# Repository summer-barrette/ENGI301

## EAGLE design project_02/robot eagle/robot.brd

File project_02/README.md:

# MOOD-DRAWING ROBOT

Hackster Project can be found at 
https://www.hackster.io/summer-barrette/mood-drawing-robot-949c22.

# STORY

My project is a mood-drawing robot. The project was inspired by the idea of 
mood rings, which are fun accessories that change color based on the 
temperature around them. My robot contains a temperature sensor that is able to 
use body heat to distinguish between times when the user is not covering the 
sensor and times when the user is covering the sensor. The robot then decides 
either that it is that it is happy (the user was covering the sensor) or sad 
(the user was not covering the sensor). Finally, using wheels connected to the 
chassis and a pen connected to a servo, the robot moves around and draws the 
user a corresponding smiley or frowny face on a standard sheet of letter paper.

# PRINTED CIRCUIT BOARD DESIGN

This repository contains the files necessary for manufacturing a printed circuit 
board for the Mood-Drawing Robot. 
*   "robot docs" contains (1) the original proposal, (2) schematics as a PDF, 
    (3) top and bottom assembly views with associated dimensions, (4) a bill of
    materials, and (5) previews of the top and bottom layer Gerber files.
*   "robot eagle" contains all the Eagle files used to build the printed circuit
    board design including (1) library of components, (2) schematics, (3) design
    rules, and (4) layout of the board.
*   "robot mfg" contains all manufacturing files including Gerber files.

# PARTS LIST

*   1 Pocket Beagle
*   1 SG90 Micro-Servo Motor
*   1 L293x Quadruple Half-H Drivers
*   2 DC Gear Motors with Smart Car Robot Plastic Tire Wheel
*   2 Buttons (Yellow and Blue)
*   1 Pen Ink Cartridge
*   1 Wooden Dowel
*   1 Printed Ciruit Board with
    * 1 Adafruit Si7021 Temperature & Humidity Sensor
    * 2 LEDs (Yellow and Blue)
    * 2 1KΩ Resistors
    * 2 10KΩ Resistors
    * 1 0.1μF Capacitor

# BUILD INSTRUCTIONS

*   Solder Through-hole Components
    * Solder PocketBeagle to PocketBeagle Outline
    * Solder Adafruit Si7021 Temperature & Humidity Sensor to U3 Outline
    * Solder L293x Quadruple Half-H Drivers to U2 Outline
    * Solder SG90 Micro-Servo Motor wires to U4 power, signal, and ground pads
    * Solder DC Gear Motors to M1 and M2 power and ground pads
*   Construct Chassis
    * Laser cut chassis vector template out of foam core
    * Using hot glue, assemble foam chassis so that 
    * (first) the wheels and back wooden dowel are between levels 1 and 2.
    * (second) the PocketBeagle and servo are between levels 2 and 3.
    * (third) the solderless breadboard is above level 3.
    * (fourth) the front wooden dowel and pen go from the ground to above 
      level 2.
    * Tie the servo to the pen with a thin wire; ensure servo pushes pen down 
      into the ground when ‘on’ and pulls pen up off the ground when ‘off’.

# OPERATION INSTRUCTIONS

1.  Turn on PocketBeagle to run the run script
    * The pins should be configured.
    * The program should initialize.
2.	Press the yellow button while either covering or not covering the 
    temperature sensor
    * The yellow LED should turn on.
    * The temperature should be recorded and the mood (happy or sad) decided.
    * The yellow LED should turn off.
3.	Set the robot in the center of a standard sheet of letter paper
    * (first) the paper is in a vertical orientation.
    * (second) the wooden dowel is on the top left corner of the paper.
    * (third) the front of the robot is facing and parallel to the top edge 
      of the paper.
4.	Press the blue button
    * The blue light should come on.
    * The robot should drive around while picking up and putting down the pen.
    * The robot should draw a frowny or smiley face.
5.	The ‘temperature’ function and ‘drawing’ function do not have to be linear. 
    This means the temperature can be re-recorded by hitting the yellow button 
    directly after the previous temperature sequence. And the robot can re-draw 
    the same smiley or frowny face by hitting the blue button directly after 
    the previous drawing sequence.

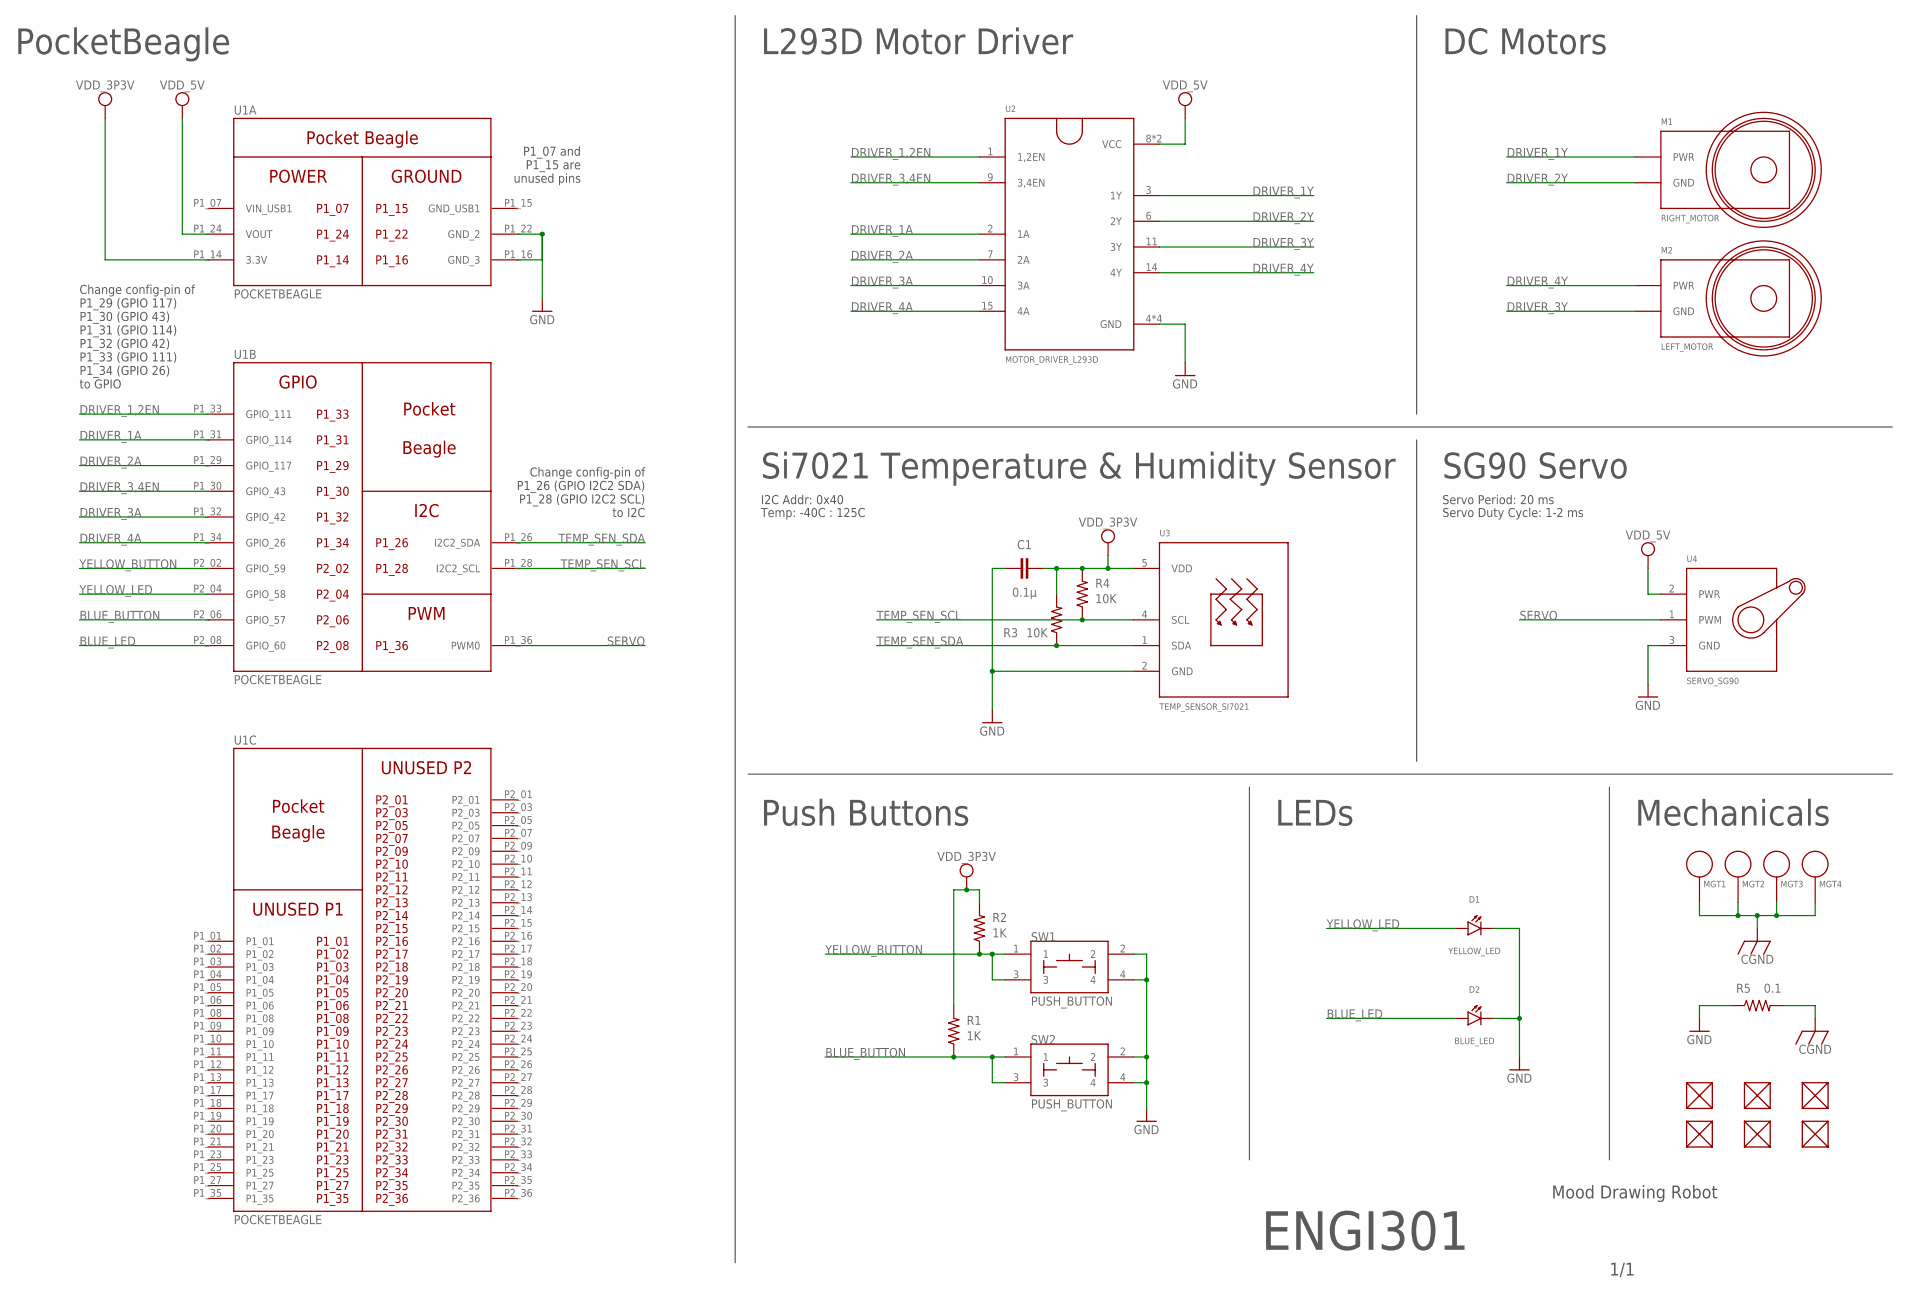
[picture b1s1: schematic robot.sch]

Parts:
C1: 0.1μ; C0603
D1: YELLOW_LED; LED_EIA_STD
D2: BLUE_LED; LED_EIA_STD
FUD1, FUD2, FUD3, FUD4, FUD5, FUD6: FIDUCIAL; FIDUCIAL_40MIL
M1: RIGHT_MOTOR; DC_MOTOR
M2: LEFT_MOTOR; DC_MOTOR
MGT1, MGT2, MGT3, MGT4: MOUNTING_HOLE
R1, R2: 1K; R0603
R3, R4: 10K; R0603
R5: 0.1; R0805
SW1, SW2: PUSH_BUTTON; PUSH_BUTTON_12.5MM
U1: POCKETBEAGLE
U2: MOTOR_DRIVER_L293D; MOTOR_DRIVER
U3: TEMP_SENSOR_SI7021; TEMP_SENSOR
U4: SERVO_SG90; SERVO

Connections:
BLUE_BUTTON: R1.1, SW2.1, SW2.3, U1.P2_06 (GPIO_57)
BLUE_LED: D2.ANODE, U1.P2_08 (GPIO_60)
CGND: MGT1.P$1, MGT2.P$1, MGT3.P$1, MGT4.P$1, R5.2
DRIVER_1,2EN: U1.P1_33 (GPIO_111), U2.1 (1,2EN)
DRIVER_1A: U1.P1_31 (GPIO_114), U2.2 (1A)
DRIVER_1Y: M1.1 (PWR), U2.3 (1Y)
DRIVER_2A: U1.P1_29 (GPIO_117), U2.7 (2A)
DRIVER_2Y: M1.2 (GND), U2.6 (2Y)
DRIVER_3,4EN: U1.P1_30 (GPIO_43), U2.9 (3,4EN)
DRIVER_3A: U1.P1_32 (GPIO_42), U2.10 (3A)
DRIVER_3Y: M2.2 (GND), U2.11 (3Y)
DRIVER_4A: U1.P1_34 (GPIO_26), U2.15 (4A)
DRIVER_4Y: M2.1 (PWR), U2.14 (4Y)
GND: C1.1, D1.CATHODE, D2.CATHODE, R5.1, SW1.2, SW1.4, SW2.2, SW2.4, U1.P1_16 (GND_3), U1.P1_22 (GND_2), U2.4 (GND), U2.5 (GND), U2.12 (GND), U2.13 (GND), U3.2 (GND), U4.3 (GND)
SERVO: U1.P1_36 (PWM0), U4.1 (PWM)
TEMP_SEN_SCL: R4.1, U1.P1_28 (I2C2_SCL), U3.4 (SCL)
TEMP_SEN_SDA: R3.1, U1.P1_26 (I2C2_SDA), U3.1 (SDA)
VDD_3P3V: C1.2, R1.2, R2.2, R3.2, R4.2, U1.P1_14 (3.3V), U3.5 (VDD)
VDD_5V: U1.P1_24 (VOUT), U2.8 (VCC), U2.16 (VCC), U4.2 (PWR)
VIN_USB1: U1.P1_07 (VIN_USB1)
YELLOW_BUTTON: R2.1, SW1.1, SW1.3, U1.P2_02 (GPIO_59)
YELLOW_LED: D1.ANODE, U1.P2_04 (GPIO_58)

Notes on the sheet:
PocketBeagle
L293D Motor Driver
DC Motors
Si7021 Temperature & Humidity Sensor
SG90 Servo
Push Buttons
LEDs
I2C Addr: 0x40
Servo Period: 20 ms
Servo Duty Cycle: 1-2 ms
1/1
Mood Drawing Robot
ENGI301
Mechanicals
Temp: -40C : 125C
Change config-pin of P1_29 (GPIO 117) P1_30 (GPIO 43) P1_31 (GPIO 114) P1_32 (GPIO 42) P1_33 (GPIO 111) P1_34 (GPIO 26) to GPIO
Change config-pin of P1_26 (GPIO I2C2 SDA) P1_28 (GPIO I2C2 SCL) to I2C
P1_07 and P1_15 are unused pins

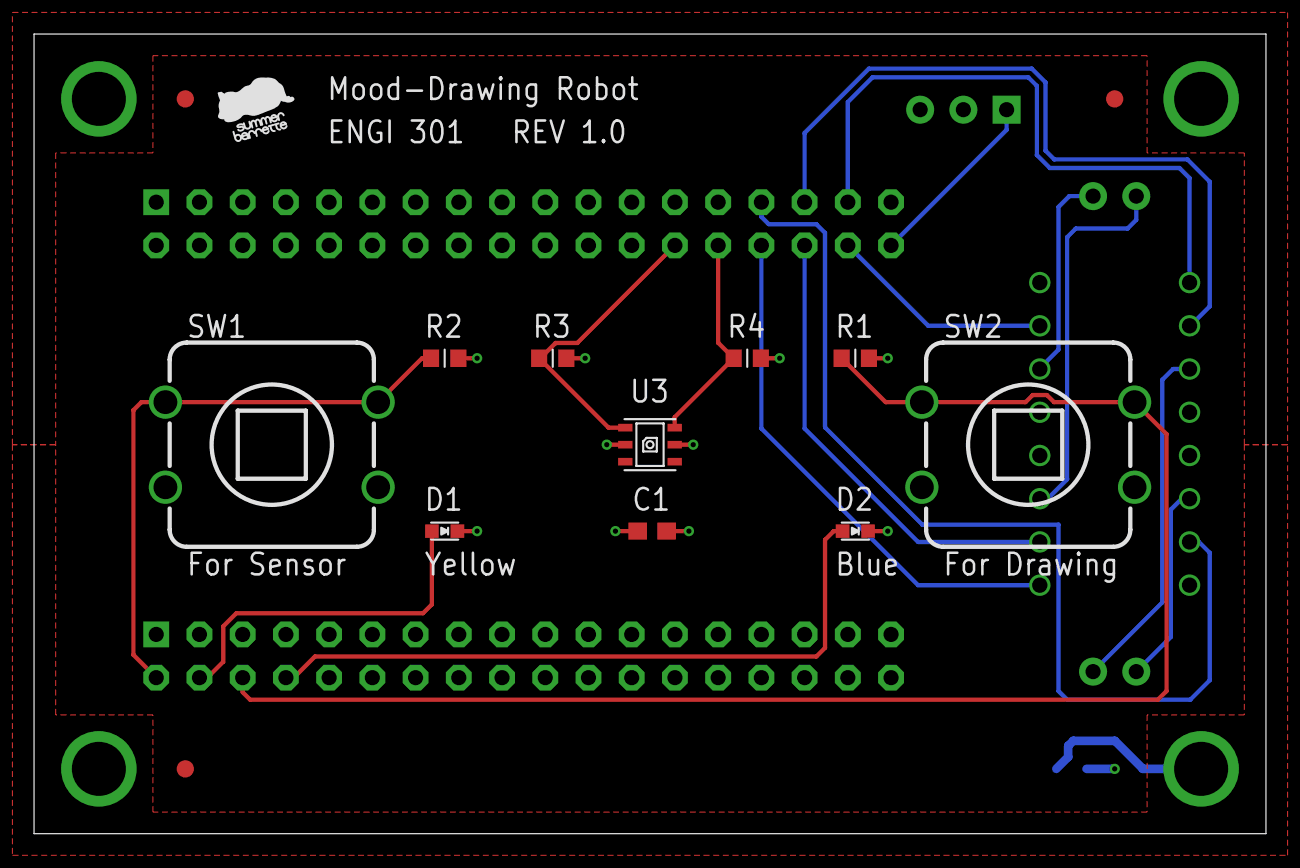
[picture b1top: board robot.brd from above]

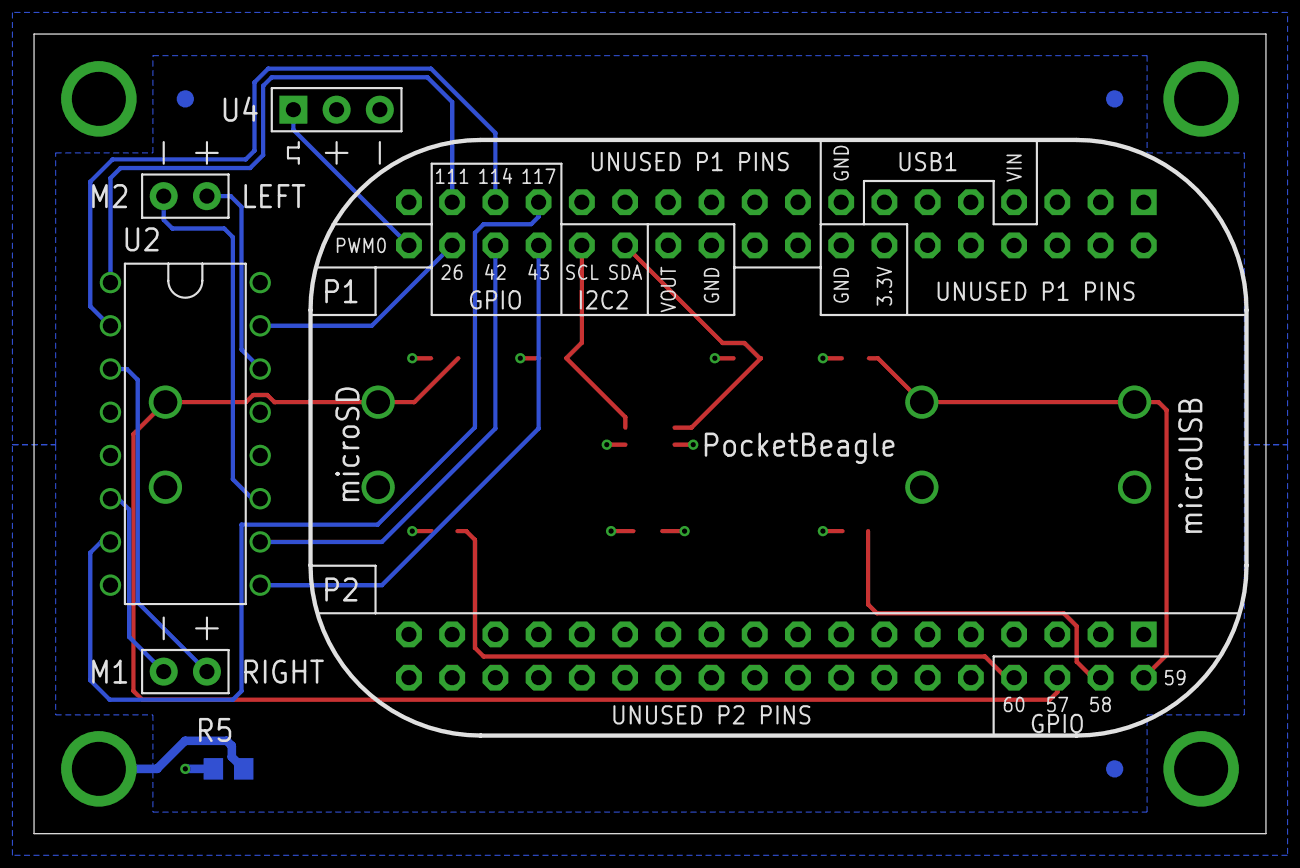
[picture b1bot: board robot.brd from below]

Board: 4 copper layers, 72.4 x 47.0 mm, 27 parts (9 on the bottom side), 21 nets.

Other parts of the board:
U$1: LOGO

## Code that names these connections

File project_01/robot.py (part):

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
SG90_FREQ   = 50                  # 20ms period (50Hz)
SG90_POL    = 0                   # Rising Edge polarity
SG90_OFF    = 5                   # 0ms pulse -- Servo is inactive
SG90_RIGHT  = 5                   # 1ms pulse (5% duty cycle)  -- All the way right
SG90_LEFT   = 10                  # 2ms pulse (10% duty cycle) -- All the way Left

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        """Setup the hardware components."""
        
        # Initialize Buttons
        GPIO.setup(self.yellow_button, GPIO.IN)
        GPIO.setup(self.blue_button, GPIO.IN)
        
        # Initialize LEDs
        GPIO.setup(self.yellow_led, GPIO.OUT)
        GPIO.setup(self.blue_led, GPIO.OUT)
        
        # Initialize Servo; Servo should be "off"
        PWM.start(self.servo, SG90_OFF, SG90_FREQ, SG90_POL)
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        while(1):
            
            # Wait for button press
            while (GPIO.input(self.yellow_button) == 1) and (GPIO.input(self.blue_button) == 1):
                pass
            
            # Yellow button pressed
            if (GPIO.input(self.yellow_button) == 0) and (GPIO.input(self.blue_button) == 1):
                
                # Record time
                yellow_button_press_time = time.time()
                
                # Wait for button release
                while(GPIO.input(self.yellow_button) == 0):
                    pass
                
                # Turn light on, measure temperature, turn light off
                if ((time.time() - yellow_button_press_time) > 0.0):
                    GPIO.output(self.yellow_led, GPIO.HIGH)
                    time.sleep(3)
                    
                    i2c = I2C(SCL_2, SDA_2)
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                    
                    print("I am", emotion)
                    
                    GPIO.output(self.yellow_led, GPIO.LOW)
            
            # Blue button pressed
            if (GPIO.input(self.yellow_button) == 1) and (GPIO.input(self.blue_button) == 0):
                
                # Record time
                blue_button_press_time = time.time()
                
                # Wait for button release
                while(GPIO.input(self.blue_button) == 0):
                    pass
                
                # Turn light on, draw shapes, turn light off
                if ((time.time() - blue_button_press_time) > 0.0):
                    
                    # Turn light on
                    GPIO.output(self.blue_led, GPIO.HIGH)
                    time.sleep(1)
                    
                    # Draw face
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                        time.sleep(1)
                    
                    # Turn light off
                    GPIO.output(self.blue_led, GPIO.LOW)
    
    # End def
    
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        """Cleanup the hardware components."""
        
        # Clean up GPIOs
        GPIO.output(self.yellow_led, GPIO.LOW)
        GPIO.output(self.blue_led, GPIO.LOW)
        
        # Clean up GPIOs
        GPIO.cleanup()
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
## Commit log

2021-09-16 Updating README.md
2021-10-05 Creating Simple Calculator
2021-10-05 Creating Blinking USR3 LED
2021-10-14 Add project proposal via upload
2021-11-02 Main Script
2021-11-02 Pin Configuration
2021-11-02 Run Script
2021-11-02 Build and Operation Instructions
2021-11-08 Pin Configurations
2021-11-17 Project Proposal
2021-11-22 Library, Schematic, and Board
2021-11-22 Library
2021-11-22 Schematic
2021-11-22 Board
2021-12-03 Design Rules
2021-12-03 Assembly
2021-12-03 Bill of Materials
2021-12-03 Manufactoring
2021-12-03 Delete
2021-12-03 Schematics
2021-12-03 ReadMe
2021-12-03 Gerber

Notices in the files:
project_01/robot.py:
License:
Copyright 2021 Summer Barrette
